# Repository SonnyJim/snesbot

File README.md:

snesbot
=======

Controlling a SNES with a Pi.
-----------------------------

The main aim of the project is to:

A.  Use USB devices connected to the Pi (joysticks etc) to control a real SNES

B.  Record and playback inputs into a real SNES

How it works:
-------------
The SNES controller protocol is fairly simple, every 16.67ms (or 60Hz for NTSC, 50Hz for PAL consoles) it sends out a latch pulse to each controller, which contain 2 x 4021 shift registers.  These shift registers then clock out the 16 bits of data to the console.  Although the latch pulse is fairly slow, the clock is fairly quick, with 16us between clock pulses.

So far so good, but what about randomness in games?  Well, the good thing is that the SNES lacks a source of entropy (hardware random number generator or even a realtime clock), so most games use an absurdly simple principle.  Count the number of latches before a controller input is pressed and use that to seed a PRNG.  Also bear in mind that the SNES doesn't start sending out the latch pulses until the CPU is working correctly, this means that as long as we send out the same button presses on exactly the same latch on each poweron, then our PRNG will act *exactly* the same, with the same enemy patterns, powerups, items etc.

My different approaches:
-----------------------

I tried a few different approaches.  I first looked up some benchmarks for the GPIO on the Pi and found that it might be possible to bitbang the SNES directly.  That approach ended in failure, mainly due to the Pi not being able to clock out the data fast enough for the SNES when it sees the latch pulse.  

The way around this was to use some chips that can handle the faster clock pulse and send the data out to the SNES controller port.

I took a cheap knock-off SNES controller (which also supplied the connector I needed for the controller port) and tried to wire up the GPIO directly to the pads, but this again ended in failure due to a combination of my shoddy soldering skills and the crapness of the PCBs, as traces were lifting everywhere.

I then tried my third approach, which was met with some success.  I duplicated the hardware inside of the SNES controller (2 x 4021 shift registers) and wired up 12 GPIO pins to that (X, Y, B, A, L, R, Up, Down, Left and Right).  

I also needed something to act as a buffer/level convertor for the latch pulse, as the output from the SNES is 5V logic whereas the GPIO pins on the Pi are only 3.3v tolerant.

To my amazement it worked and it was detected as a proper controller the Nintendo Controller Test software!

Live input was working fine, both from a USB keyboard and a PS1 controller connected via a USB adapter, but recording and playback would lose sync after a few button presses, which was slightly disheartening.  Perhaps all those people telling me that I wouldn't be able to make it work with the overhead of Linux were right and I've have to change my approach again to use a microcontroller instead.

After a bit more playing around I had a bit of a eureka moment, where I found out that I was supplying the 4021's with 3.3V instead of 5V.  Also I hadn't put in a blocking diode to stop current flow back into the SNES.  Once I had fixed both of these problems playback worked a *lot* better.  I'm not quite sure why live input worked and recorded didn't at 3.3V, but I'm certainly glad it's working at 5V!

Flash forward 2 years......
---------------------------

I picked up the project again after getting back into SNES collecting and decided to try another way.  I wasn't really happy with using so much of the Pi's GPIO, so I explored some other options.  The author of the WiringPi library pointed me in the direction of the MCP23017 port expander chip.  The good thing about this chip is that it allows 16bits of input/ouput at 5V and can communicate with the Pi using I2C, which is 3.3v.  This is a very good thing, as it allows me to drive 16bits of data at 5V using only 2 lines from the Pi (SDA/SCL), which will be at 3.3v.  No more level shifter chips, huzzah (well nearly).  I still need to level shift the latch input from the SNES into the Pi, but I can do that very simply with a voltage divider.  It also means that to add another player it means just adding another 3 chips (1 x MCP23017, 2 x 4021's) and can use the same I2C line from the Pi, just set to different addresses.

Reading SNES joysticks
----------------------

Now that I had some spare GPIOs, I may as well make some use of them!  In the wiringPi library there is support for reading NES joysticks.  This is a good thing, as the NES joystick protocol is identical to the SNES one, just that the SNES protocol uses more bits for the extra buttons.  Another bonus is that all of the SNES joysticks I tried would run quite happily at 3.3v, meaning I could hook them straight into the Pi without needing to level shift them.  Double result!

This means that I can now operate the Pi in 'Passthrough' mode, where I read the SNES joystick inputs into the Pi, then load up the shift registers with that data using the MCP23017 which is then clocked into the SNES.  Because I am intecepting the joystick inputs I can:

* Hide the Pi inside the SNES case
* Use a ribbon cable to pass the controller data into the Pi and out again into the SNES, no more messy soldering onto the back of the SNES controller input block.

TAS Videos
----------

So I was at the stage where I could playback from my own playback format and was successful with roughly 90% of the games I tried.  So it was time to look at working on using emulator movie files.  These are files recorded by the emulator that are used to playback high score attempts/speed runs etc.  Sometimes emulators are used to create bizarre and lightning quick videos called 'Tool Assisted Speedruns'.  These would be a good source of videos to demonstrate the abilities of SNESBot.  To try and get things to work first time, I went the simple route.  I chose a TAS video that had previously been verifed on hardware, which was the KFC-Mario speedrun of Super Mario All-Stars: Super Mario Bros. Lost levels.  Because I was intending to run on hardware, I would need to use a pretty accurate emulator, so lsnes looked like a good candidate.  I found a Lua script by Ilari to output the controller data I needed for the emulator and wrote some importing code for my bot.  After a few false starts, ILari was particulary helpful in getting it working.  So I was at the stage where I coulld give this TAS video a try.

I grabbed my copy of SMAS, plugged it in and it went through the title screens, Mario started to run and then.

Nothing.  He just sat there hopping on the spot and generally not doing what I wanted him to do.

This was slightly annoying, so I tried it with the console in PAL rather than NTSC, still the same.  I took my SNES apart and saw the one of the legs of PPU2 had snapped off after I installed a SuperCIC mod.  I believe this was causing it to run in permenant PAL mode, throwing off the timings.  With a bit of delicate surgery, I managed to get it soldered back on, setup again and hit start.  And I watched Mario go absolutely nuts for 33 minutes, flying impossibly through levels, then destroy Bowser and complete the game.

Feeling rather pleased. my next stop was to write an importer for SNES9X emulator movie files, which hasn't worked out so well.  Which is a shame, as was a popular file format, with a lot of TAS runs available.  Because the TAS videos rely on very sharp timing, if the emulation isn't exactly the same as a SNES, the frames 'desync' and the Pi/SNES lose sync with each other.

This normally happens during a 'lag frame', which is a frame where the SNES CPU is too busy to poll the joystick inputs, because it's too busy drawing enemies exploding etc.  The reason lsnes input files work and SNES9x files don't is down to the way they emulate these lag frames.

I really need to get myself a logic analsyer as so far I've been doing this 'blind'.

Hardware required:
------------------
A Raspberry Pi + SD card

1 x MCP23017 Port Expander
2 x CD4021B CMOS shift registers

1 x buffer / level convertor for the latch pulse

Some perf/vero board to mount it all on

An old floppy cable or something to break out the GPIO pins

A knockoff/broken controller for the SNES connector

Software needed:
----------------
Raspbian
WiringPi library by gordonDrogon

Games confirmed to be working:
------------------------------
Assault Suit Vulcan

Contra 3: The Alien Wars

Earthworm Jim

UN Squadron

Super Mario Kart

Wagyan Paradise

Killer Instinct

Street Fighter 2

Street Fighter 2: Turbo

Super Mario All-Stars

Super Mario Kart

Super Mario World 2: Yoshis Story

SuperGB JPN + Tetris DX

SuperGB JPN + Tetris

Super R-Type

Games that don't work
---------------------

NBA Jam

Super Tennis

Speedy Gonzales

Why they don't work is a bit of a mystery to me at the moment.  As the code that reads the controller interrupts isn't the same for each game, it could be that my bot isn't precise enough with the timings.  Also some games use uninitialised memory as the seed for the PRNG, which means the game won't be exactly the same with the same inputs.  I'll have to run through them with a SNES debugger at some point

Features:
---------
Input via USB and real SNES controller via GPIO.

Record joystick inputs and playback

Tool Assisted Video playback via lsnes and Ilari's polldump.lua script

To Playback a lsnes TAS video:
------------------------------
Download lsnes video from TASVideos.org (lsmv)

Download lsnes emulator and install, make sure you download a version that supports on_latch()

Download polldump.lua script

Start lsnes emulator, load ROM, pause and reset console

Load lua script

Type in the messages window:

L start_dump ("filename")

and press 'Execute'

Start playback

The dump file will be saved automatically at the end of playback, but if you want to finish early, type:

L end_dump ()

and press 'Execute'

Copy the .rec and .sub files to the Pi

Load with:

sudo ./snesbot -p -f filename.rec

Turn on SNES and hopefully watch it do incredible things

I have included a script for snes9x-rr, but unfortunately it seems that the emulation isn't accurate enough, especially if there are 'lag frames' during gameplay.

TODO:
----
Support for more than 1 controller

Netplay (depending on the RNG method used by each game)

LED sign output to display subtitles

Support other TAS video files other than lsnes

Add support for SNES mouse via a USB mouse attached to the Pi.

Find out why some games don't work

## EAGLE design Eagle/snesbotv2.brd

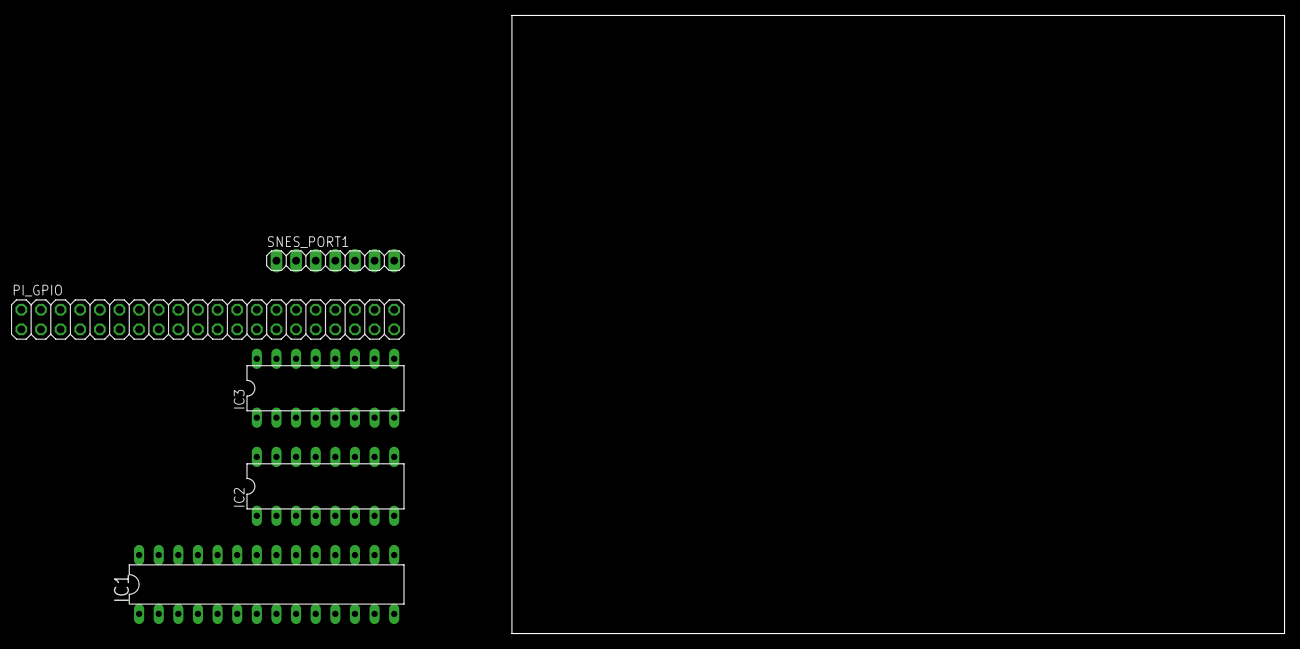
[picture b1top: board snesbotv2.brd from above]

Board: 2 copper layers, 100.0 x 80.0 mm, 5 parts (0 on the bottom side), 9 nets, no tracks yet.

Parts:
IC1: MCP23017SP; DIL28-3
IC2, IC3: 4021N; DIL16
PI_GPIO: 2X20
SNES_PORT1: 1X07

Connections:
unnamed: IC2.10, IC3.10, SNES_PORT1.2
unnamed: IC2.9, IC3.9, SNES_PORT1.3
unnamed: IC1.10, IC1.15, IC1.16, IC1.17, SNES_PORT1.7
unnamed: IC1.9, IC1.18, PI_GPIO.2
unnamed: IC1.12, PI_GPIO.5
unnamed: IC1.13, PI_GPIO.3
unnamed: IC3.1, IC3.13, IC3.14, IC3.15
VDD: IC2.16, IC3.16
VSS: IC2.8, IC3.8

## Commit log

2013-09-21 More work
2013-09-21 Simple Makefile
2013-09-21 Strangeness
2013-09-22 More progress
2013-09-22 Add options
2013-09-22 Add signalling for graceful-ish exit
2013-09-22 Timings need fiddling with
2013-09-22 Working controller detection
2013-09-22 Getting there slowly
2013-09-22 Adjust priority
2013-09-22 Optimise a bit
2013-09-22 Nearly there
2013-09-23 Tidy up
2013-09-23 Try using interrupts
2013-09-24 More work on interrupts
2013-09-24 Why?
2013-09-24 Simple controller timing test program
2013-09-24 Update snestest
2013-09-24 Add in results of snestest from various carts
2013-09-25 Tidy up snestest
2013-09-30 It works! Wired up 2 x 4021 shift registers and I can now pass the Nintendo Controller test :-)
2013-09-30 snesbot.c
    Switch to /dev/input method as SDL sucks
2013-09-30 Working /dev/input/event0, one key at a time though
2013-10-01 Weird event results
2013-10-01 Fix stupid keyboard reads
2013-10-01 It passed the official Nintendo Controller Test program
2013-10-01 Tidy up code
2013-10-01 Add joystick support
2013-10-01 Debug joystick code, remove moonwalking ability
2013-10-01 Initial recording support
2013-10-01 More work on recording
2013-10-01 Work on argc/argv
2013-10-02 More tidying up
2013-10-02 Remove ugly EOF code
2013-10-02 Using unbuffered I/O
2013-10-02 Change playback to use malloc/memcpy
2013-10-02 ChOops, typo
2013-10-03 Reorganise code
2013-10-03 Switching recording to buffer
2013-10-03 Fix stupid typo
2013-10-03 Another stupid typo
2013-10-03 Nearly working
2013-10-04 Try to optimise filepos
2013-10-04 Add in debug print for inputs
2013-10-04 More debug information
2013-10-04 More updates to the readme
2013-10-04 Update snestest.c for the newer hardware
2013-10-04 Update Makefile
2013-10-07 Change playback inputs to be interrupt driven
2013-10-07 Is it working? Maybe.
2013-10-07 Nearly there (again)
2013-10-08 Tidying up
2013-10-09 Add header file
2013-10-09 Working, but losing sync after a few minutes
2013-10-09 Record buffer was set to 16KB, not 16MB
2013-10-09 Add schematic
2013-10-10 Improve program flow a bit
2013-10-10 Print time elapsed during record/playback
2013-10-11 Fix a few bugs with debug playback
2013-10-11 Increase size of latch counters
2013-10-11 Switch to getopt.h
2013-10-11 Initial lsnes polldump.lua support
2013-10-12 Fix byte ordering on lsnes input, thanks Ilari!
2013-10-12 Add polldump.lua script by Ilari
2013-10-12 Format README.md
2013-10-13 Initial import of snes9x lua convertor
2013-10-13 Add option to adjust whereabouts in the playback file we start
2013-10-15 Bit of debugging
2013-10-15 Tidy up and add license
2013-10-15 Add in signal handling
2013-10-15 Add header to snesbot.rec files
2013-10-15 Tidyup Makefile
2013-10-16 Add in support for recording at end of playback
2013-10-16 Debug command line parser
2013-10-16 Debug recording after playback
2013-10-17 Fix latch counter bug with playback
2016-02-21 Initial import of snesbot v2
2016-02-21 More work on v2
2016-02-21 Working record and playback
2016-02-21 Add in SNES vcc reading
2016-02-22 Refactor recording code
2016-02-22 Move joystick code
2016-02-22 Update lua script to work with new bot
2016-02-23 Refactor code, tidy up
2016-02-23 Adding in incomplete schematics for board v2
2016-02-24 Working lsnes playback
2016-02-24 Two TAS runs working, SMAS-LL and SMW
2016-02-25 Detect a Pi
2016-02-25 Initial USB joystick code
2016-02-25 More USB stuff
2016-02-26 Fix up for merge
2016-02-26 Adding in joystick test program
2016-02-27 Working USB joystick
2016-02-27 Working joystick configurator
2016-02-27 Add in PID file checking
2016-02-28 Added in simple macros/subtitle playback
2016-02-28 Fix subtitle file loading
2016-02-28 Fix stupid mistake
2016-02-29 Update polldump to dump subs and handle movie end properly
2016-02-29 Big tidy up
2016-02-29 Move macro stuff to a separate file
2016-02-29 Rename and reorganise
2016-02-29 initial import of Bizhawk dump script
2016-03-04 More reorganising
2016-03-04 Whoopsy daisy
2016-03-08 Add in joystick deadzone/configuration
2016-03-08 More work on macros/general cleanup
